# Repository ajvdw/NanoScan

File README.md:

# NanoScan
 Keyboard Matrix Scanner (6x6) based on Arduino Nano

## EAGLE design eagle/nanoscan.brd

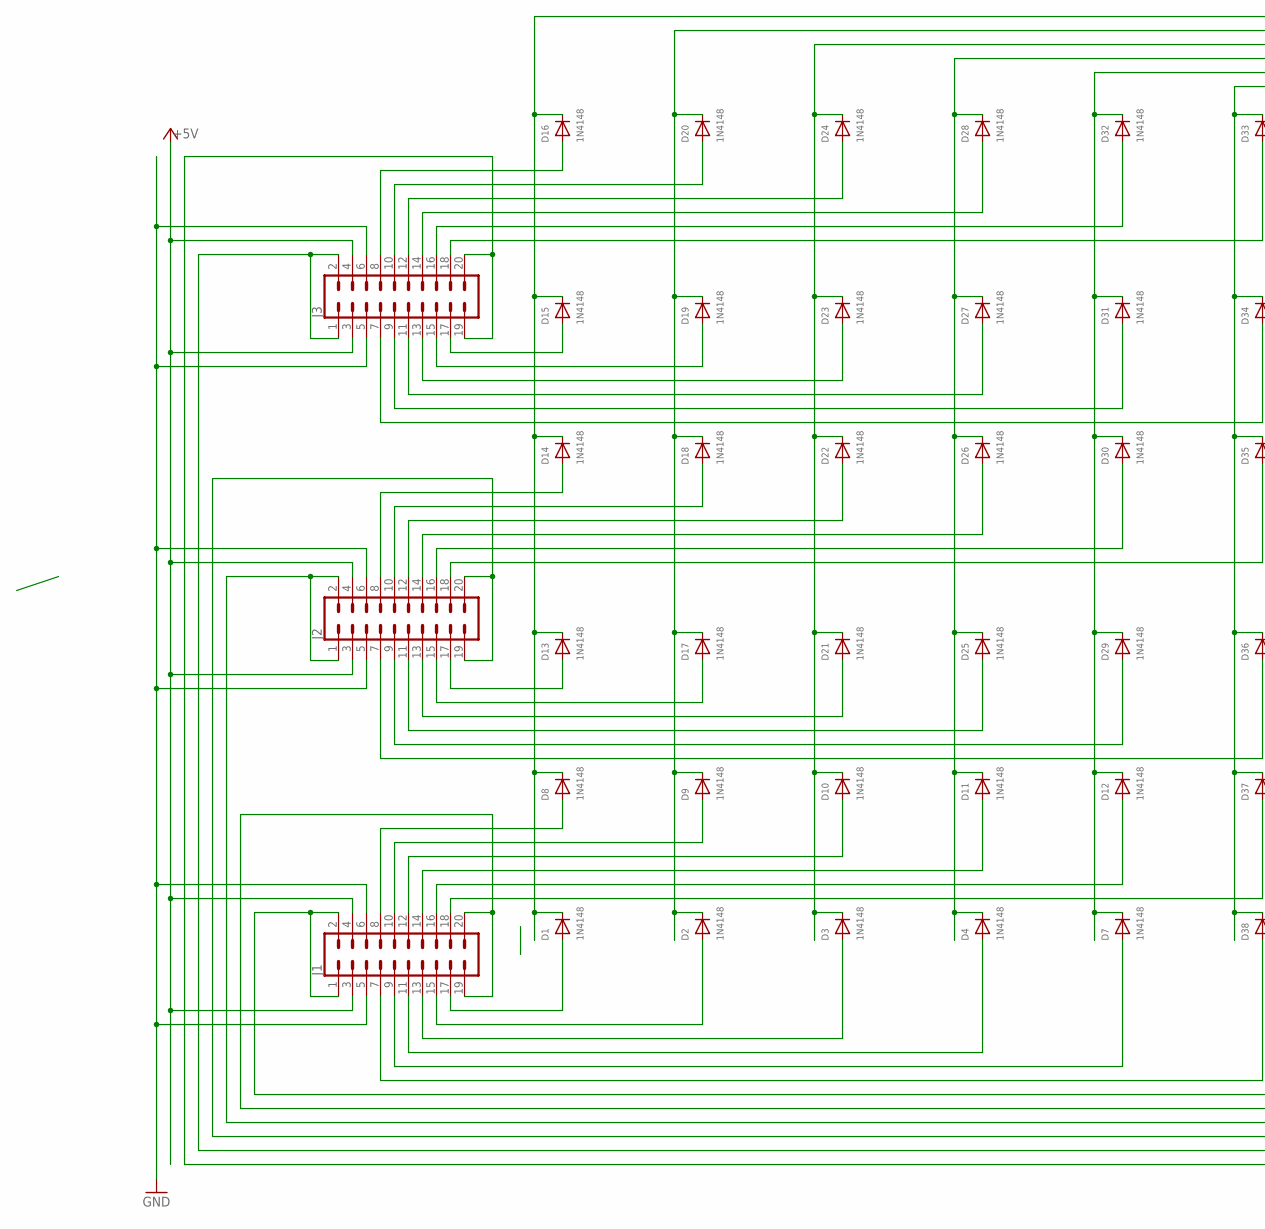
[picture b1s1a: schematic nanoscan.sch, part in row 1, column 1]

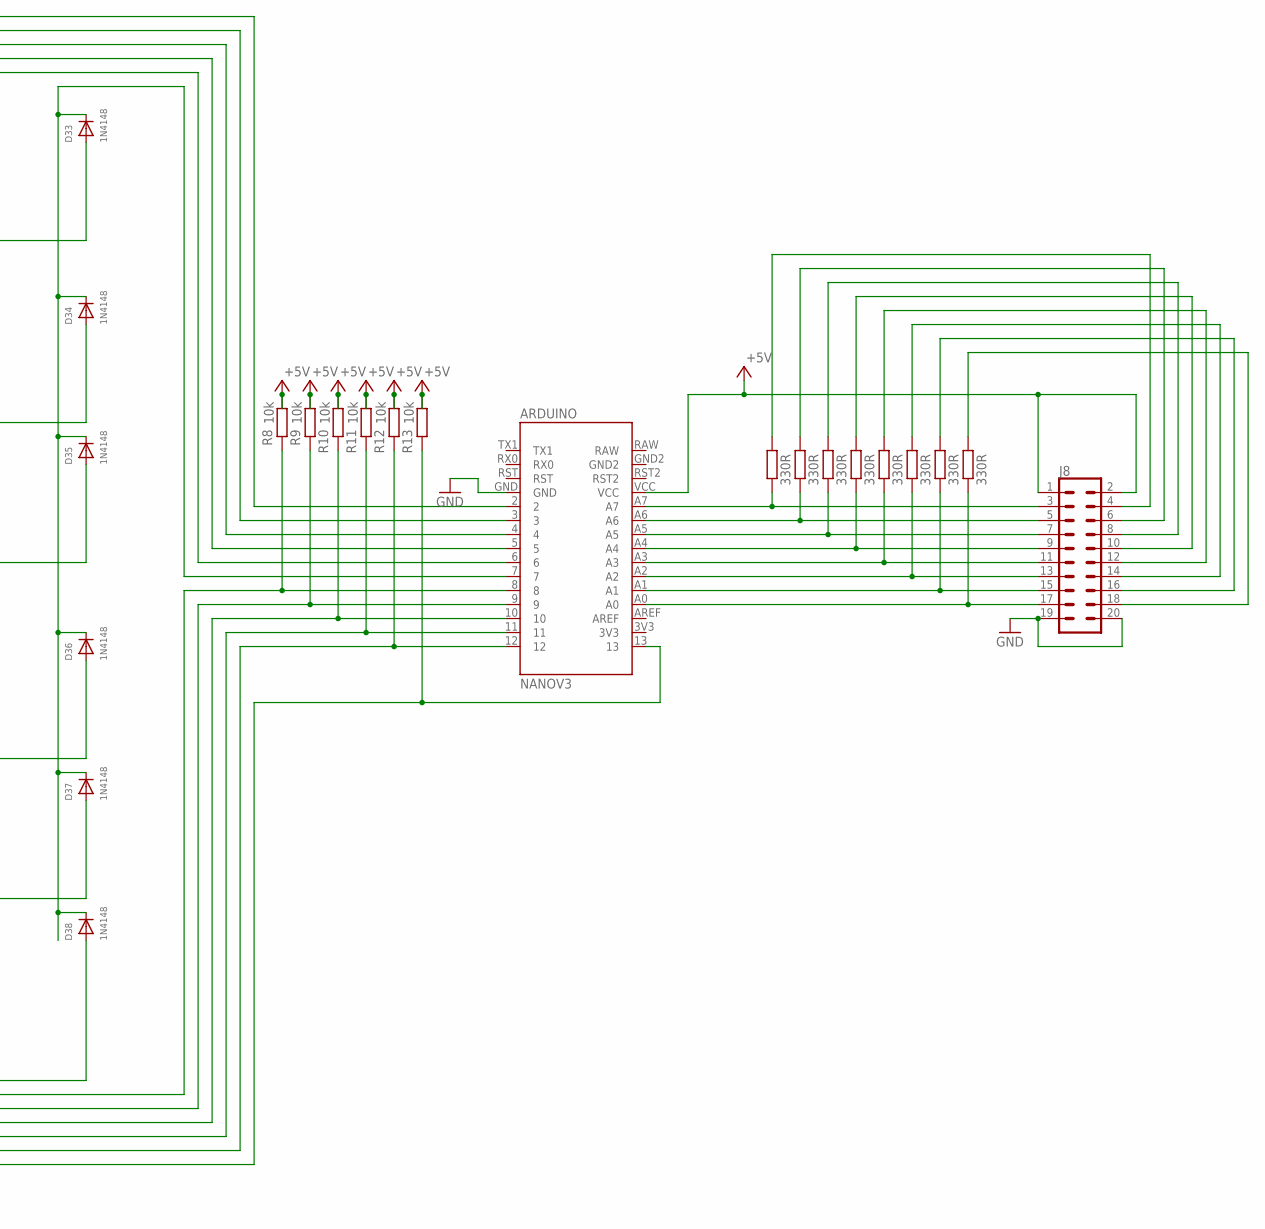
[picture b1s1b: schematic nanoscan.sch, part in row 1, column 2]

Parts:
ARDUINO: NANOV3
D1, D2, D3, D4, D7, D8, D9, D10, D11, D12, D13, D14, D15, D16, D17, D18, D19, D20, D21, D22, D23, D24, D25, D26, D27, D28, D29, D30, D31, D32, D33, D34, D35, D36, D37, D38: 1N4148; DO-1N4148
J1, J2, J3, J8: CONN_10X2SPECIAL; 2X10_LOCK_SPECIAL
R0, R1, R2, R3, R4, R5, R6, R7: 330R; 0207/10
R8, R9, R10, R11, R12, R13: 10k; 0207/10

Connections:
+5V: ARDUINO.VCC, J1.3, J1.4, J2.3, J2.4, J3.3, J3.4, J8.1, J8.2, R8.1, R9.1, R10.1, R11.1, R12.1, R13.1
GND: ARDUINO.GND, J1.5, J1.6, J2.5, J2.6, J3.5, J3.6, J8.19, J8.20
unnamed: ARDUINO.6, D7.C, D12.C, D29.C, D30.C, D31.C, D32.C
unnamed: ARDUINO.2, D1.C, D8.C, D13.C, D14.C, D15.C, D16.C
unnamed: ARDUINO.5, D4.C, D11.C, D25.C, D26.C, D27.C, D28.C
unnamed: D33.A, J3.18
unnamed: D32.A, J3.16
unnamed: D28.A, J3.14
unnamed: D24.A, J3.12
unnamed: D20.A, J3.10
unnamed: D16.A, J3.8
unnamed: D34.A, J3.7
unnamed: D31.A, J3.9
unnamed: D27.A, J3.11
unnamed: D23.A, J3.13
unnamed: D19.A, J3.15
unnamed: D15.A, J3.17
unnamed: D35.A, J2.18
unnamed: D30.A, J2.16
unnamed: D26.A, J2.14
unnamed: D22.A, J2.12
unnamed: D18.A, J2.10
unnamed: D14.A, J2.8
unnamed: D38.A, J1.7
unnamed: D7.A, J1.9
unnamed: D4.A, J1.11
unnamed: D3.A, J1.13
unnamed: D2.A, J1.15
unnamed: D1.A, J1.17
unnamed: D37.A, J1.18
unnamed: D12.A, J1.16
unnamed: D11.A, J1.14
unnamed: D10.A, J1.12
unnamed: D9.A, J1.10
unnamed: D8.A, J1.8
unnamed: D36.A, J2.7
unnamed: D29.A, J2.9
unnamed: D25.A, J2.11
unnamed: D21.A, J2.13
unnamed: D17.A, J2.15
unnamed: D13.A, J2.17
unnamed: ARDUINO.9, J1.19, J1.20, R9.2
unnamed: ARDUINO.12, J3.1, J3.2, R12.2
unnamed: ARDUINO.13, J3.19, J3.20, R13.2
unnamed: ARDUINO.10, J2.1, J2.2, R10.2
unnamed: ARDUINO.8, J1.1, J1.2, R8.2
unnamed: ARDUINO.11, J2.19, J2.20, R11.2
unnamed: ARDUINO.A7, J8.3, R7.1
unnamed: ARDUINO.A6, J8.5, R6.1
unnamed: ARDUINO.A5, J8.7, R5.1
unnamed: ARDUINO.A4, J8.9, R4.1
unnamed: ARDUINO.A3, J8.11, R3.1
unnamed: ARDUINO.A2, J8.13, R2.1
unnamed: ARDUINO.A1, J8.15, R1.1
unnamed: ARDUINO.A0, J8.17, R0.1
unnamed: J8.18, R0.2
unnamed: J8.16, R1.2
unnamed: J8.14, R2.2
unnamed: J8.12, R3.2
unnamed: J8.10, R4.2
unnamed: J8.8, R5.2
unnamed: J8.6, R6.2
unnamed: J8.4, R7.2
unnamed: ARDUINO.3, D2.C, D9.C, D17.C, D18.C, D19.C, D20.C
unnamed: ARDUINO.4, D3.C, D10.C, D21.C, D22.C, D23.C, D24.C
unnamed: ARDUINO.7, D33.C, D34.C, D35.C, D36.C, D37.C, D38.C

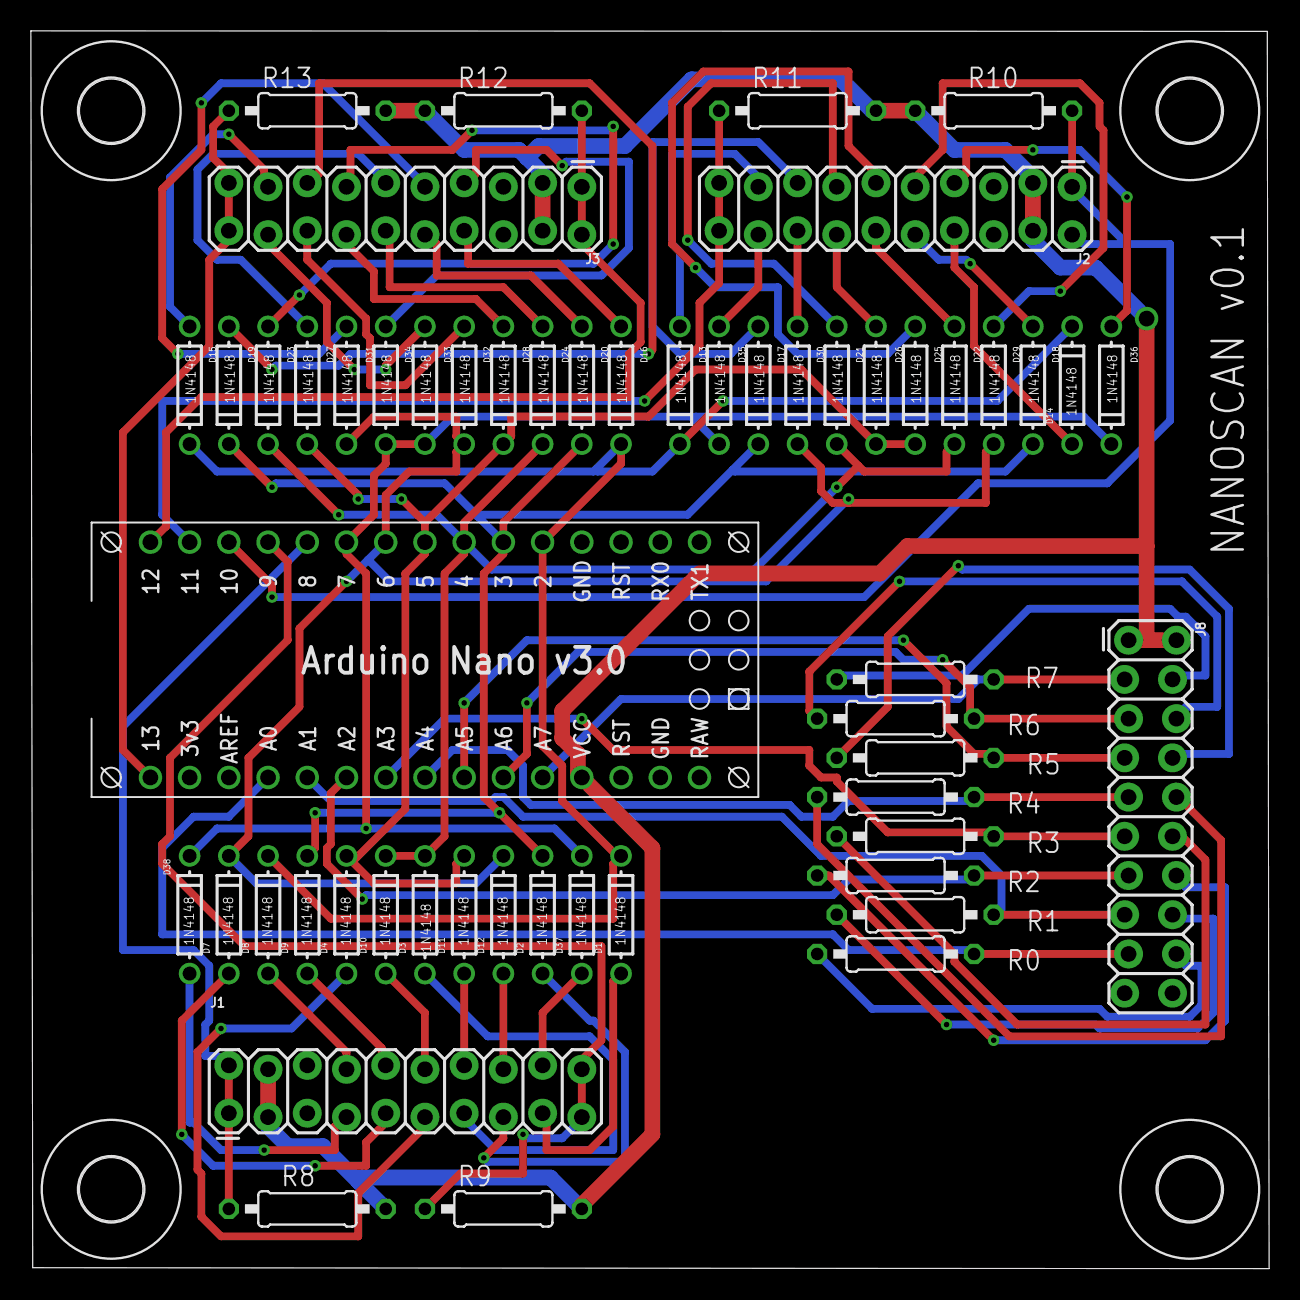
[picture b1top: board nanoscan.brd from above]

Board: 4 copper layers, 80.2 x 80.2 mm, 59 parts (0 on the bottom side), 66 nets.

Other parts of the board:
U$1, U$2, U$3, U$4: 4,1

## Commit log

2020-09-15 pcb v0.1
2020-09-23 Untested initial commit

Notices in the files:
parts and their libraries:
SparkFun-Connectors: Licensing: Creative Commons ShareAlike 4.0 International - https://creativecommons.org/licenses/by-sa/4.0
